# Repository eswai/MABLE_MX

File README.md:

# MABLE

MABLEはワイヤレス、左右分割、36キーのコンパクトなキーボードです。
キーボードカレンダー2024年3月に掲載されました。

* MiniAxe互換キーレイアウト
* 省電力なnRF52840採用
* Bluetooth接続、電池内蔵の完全ワイヤレス
* USB-Cからバッテリー充電 (リチウムポリマー電池の取り扱いにはご注意ください)
* ZMK firmwareもしくはKMK firmware
* 3Dプリンタ製のケース

## BOM

遊舎工房、TALP KEYBOARD、スイッチサイエンス(SS)、千石電商などで入手可能です。(2024/10時点で欠品の部品がいくつかありました)

| TH   | TH   | 数量 | 入手先 |
| ---- | ---- | ---- | ---- |
| PCB   | オリジナル   | 左右各1   | |
| マイコン | Seeed Studio XIAO nRF52840 | 2 | |
| バッテリー | リチウムイオンポリマー電池110mAh DPTL-DTP401525 | 2 | SS |
| バッテリーコネクタ | JST製2ピンPHコネクタ用ソケット JST-S2B-PH-K-S  | 2   | SS |
| キーキャップ| MXスイッチ用1Uサイズ|36| |
| キースイッチ | Cherry MX互換スイッチ | 36 | |
| スイッチソケット | MXスイッチ用 Kailh PCBソケット | 36 | |
| ダイオード | 1N4148 ダイオード (SMD) | 36 | |
| スライドスイッチ | 小型スライドスイッチ 1回路2接点(面実装タイプ)  SSW1P2T-SMT | 2 | 千石 |
| ケース | 3Dプリンタ製 | 1セット (6部品)   | |
| ねじ | M2 L=6   | 10  | |
| ゴム足 | 3M クッションゴム 9.5x3.8mm 丸形 CS-02 透明 | 8  | |

## 組み立て

TBD

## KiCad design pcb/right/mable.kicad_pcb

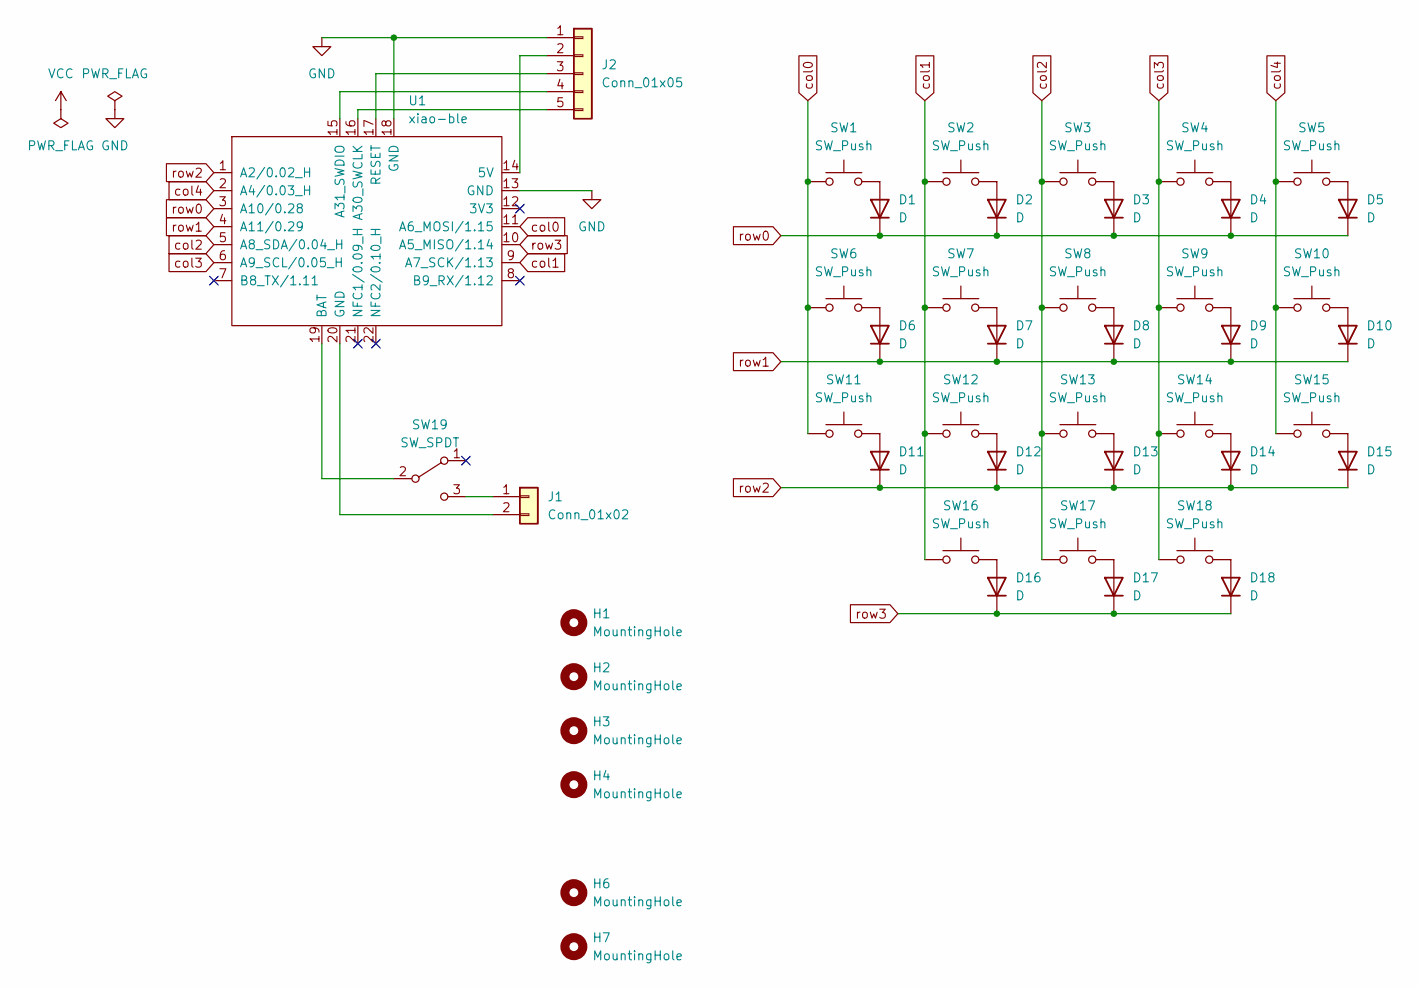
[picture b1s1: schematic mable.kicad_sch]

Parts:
D1, D2, D3, D4, D5, D6, D7, D8, D9, D10, D11, D12, D13, D14, D15, D16, D17, D18: D; D_SOD-123F
H1, H2, H3, H4, H6, H7: MountingHole; MountingHole_2.2mm_M2
J1: Conn_01x02; JST_PH_B2B-PH-K_1x02_P2.00mm_Vertical
J2: Conn_01x05; PinHeader_1x05_P2.54mm_Vertical
SW1, SW2, SW3, SW4, SW5, SW6, SW7, SW8, SW9, SW10, SW11, SW12, SW13, SW14, SW15, SW16, SW17, SW18: SW_Push; MX-Hotswap-1U
SW19: SW_SPDT; SSW1P2T-SMT
U1: xiao-ble; xiao-ble-tht

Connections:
GND: J2.1, U1.13 (GND), U1.18 (GND)
unnamed: D1.2 (A), SW1.2
unnamed: D2.2 (A), SW2.2
unnamed: D3.2 (A), SW3.2
unnamed: D4.2 (A), SW4.2
unnamed: D5.2 (A), SW5.2
unnamed: D6.2 (A), SW6.2
unnamed: D7.2 (A), SW7.2
unnamed: D8.2 (A), SW8.2
unnamed: D9.2 (A), SW9.2
unnamed: D10.2 (A), SW10.2
unnamed: D11.2 (A), SW11.2
unnamed: D12.2 (A), SW12.2
unnamed: D13.2 (A), SW13.2
unnamed: D14.2 (A), SW14.2
unnamed: D15.2 (A), SW15.2
unnamed: D16.2 (A), SW16.2
unnamed: D17.2 (A), SW17.2
unnamed: D18.2 (A), SW18.2
unnamed: J1.1, SW19.3 (C)
unnamed: J1.2, U1.20 (GND)
unnamed: J2.2, U1.14 (5V)
unnamed: J2.3, U1.17 (RESET)
unnamed: J2.4, U1.15 (A31_SWDIO)
unnamed: J2.5, U1.16 (A30_SWCLK)
unnamed: SW19.2 (B), U1.19 (BAT)
col0: SW1.1, SW6.1, SW11.1, U1.11 (A6_MOSI/1.15)
col1: SW2.1, SW7.1, SW12.1, SW16.1, U1.9 (A7_SCK/1.13)
col2: SW3.1, SW8.1, SW13.1, SW17.1, U1.5 (A8_SDA/0.04_H)
col3: SW4.1, SW9.1, SW14.1, SW18.1, U1.6 (A9_SCL/0.05_H)
col4: SW5.1, SW10.1, SW15.1, U1.2 (A4/0.03_H)
row0: D1.1 (K), D2.1 (K), D3.1 (K), D4.1 (K), D5.1 (K), U1.3 (A10/0.28)
row1: D6.1 (K), D7.1 (K), D8.1 (K), D9.1 (K), D10.1 (K), U1.4 (A11/0.29)
row2: D11.1 (K), D12.1 (K), D13.1 (K), D14.1 (K), D15.1 (K), U1.1 (A2/0.02_H)
row3: D16.1 (K), D17.1 (K), D18.1 (K), U1.10 (A5_MISO/1.14)

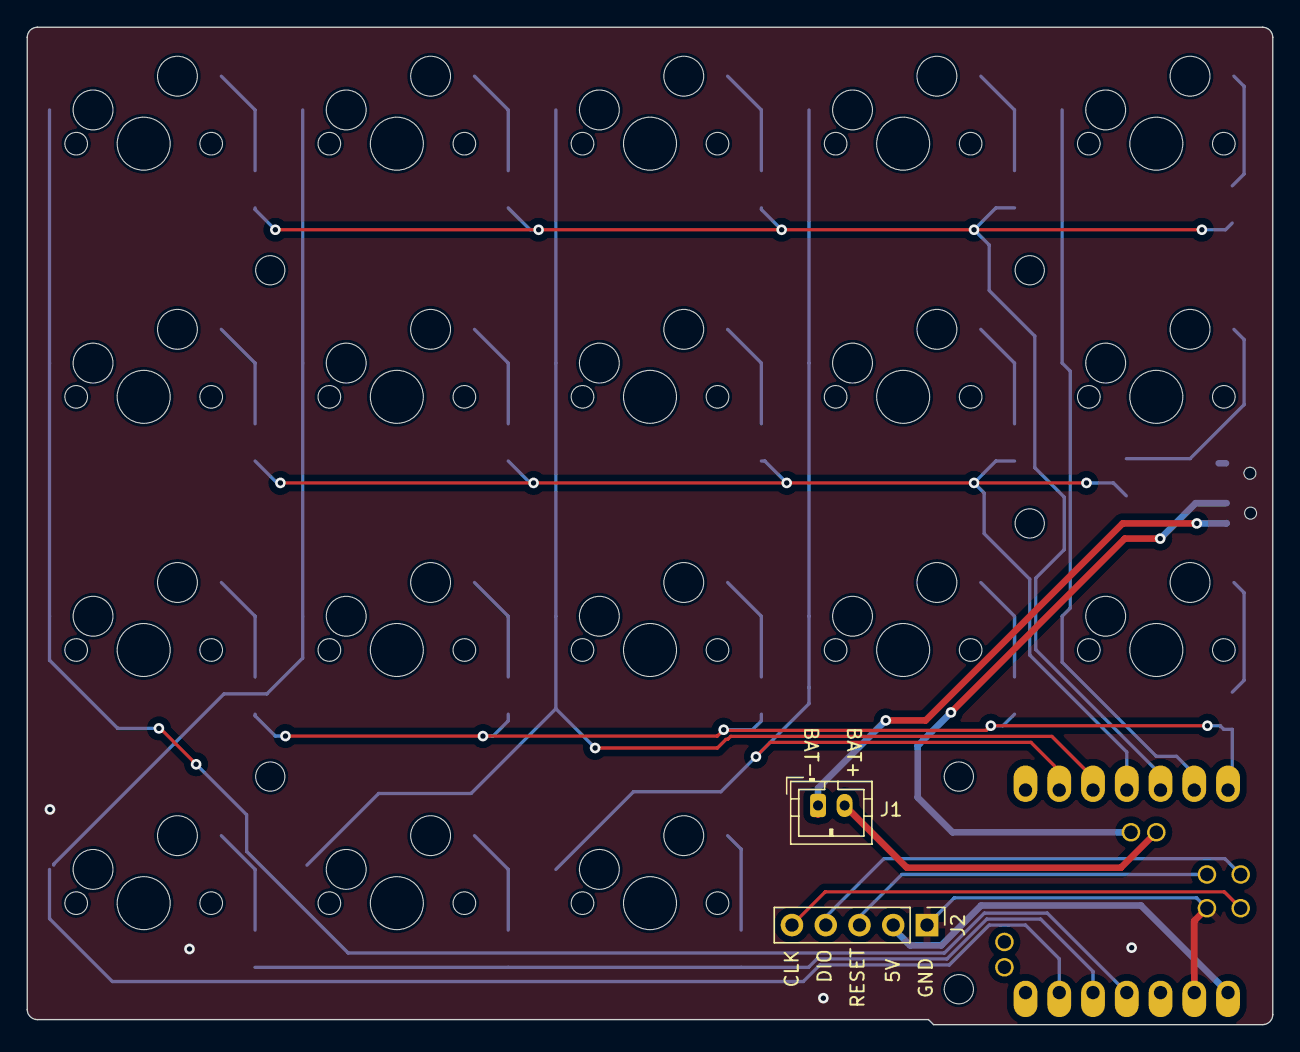
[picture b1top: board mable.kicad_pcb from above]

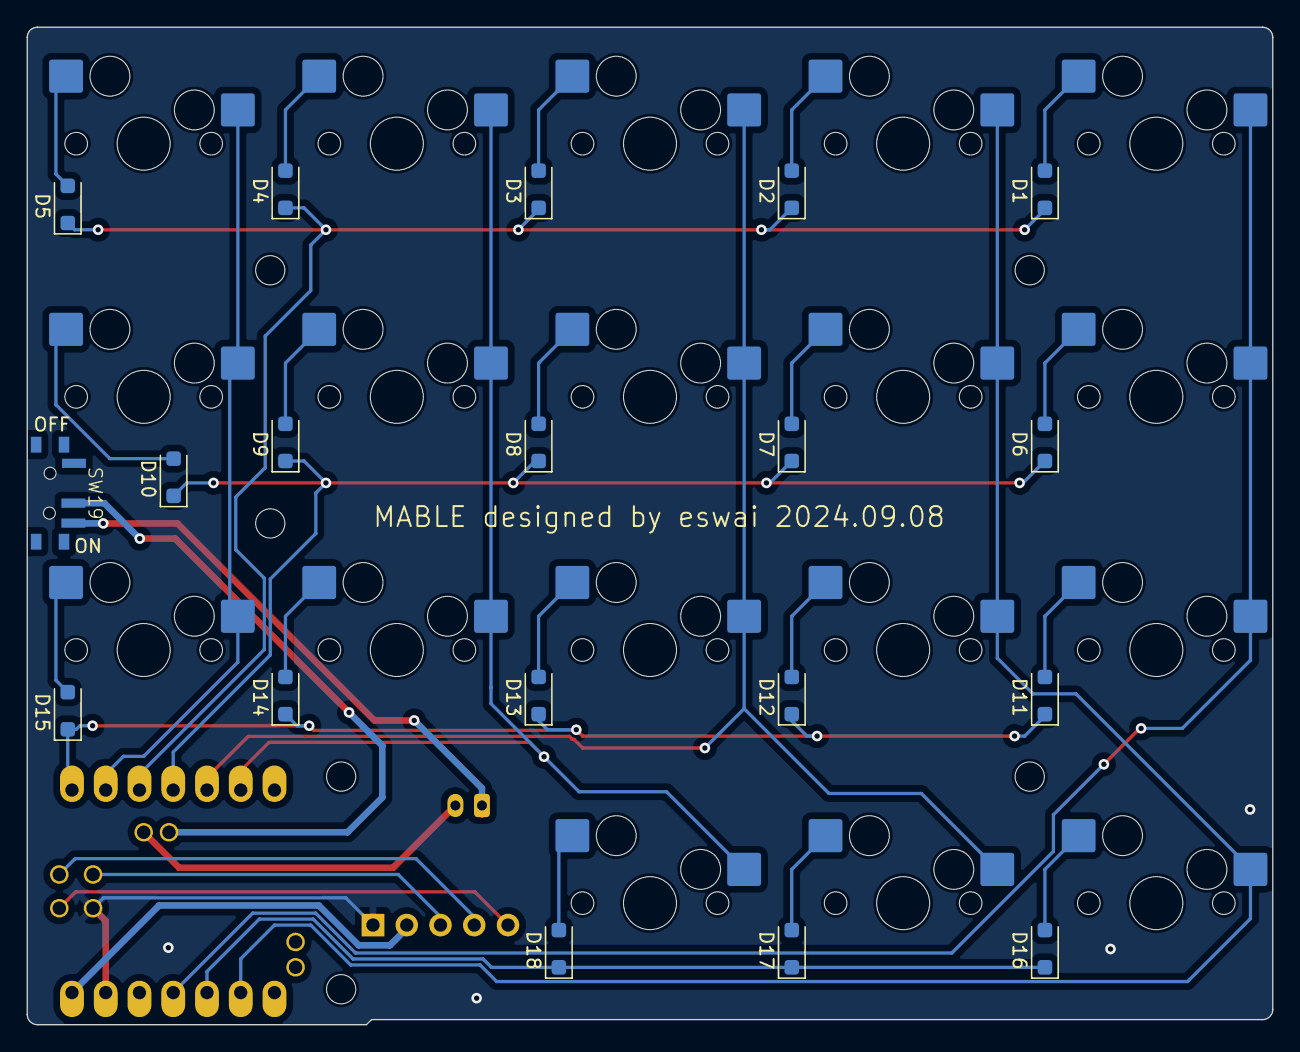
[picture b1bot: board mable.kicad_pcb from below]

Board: 2 copper layers, 93.7 x 75.1 mm, 46 parts (19 on the bottom side), 35 nets.

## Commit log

2024-10-19 ライセンス、画像
2024-10-27 readme
